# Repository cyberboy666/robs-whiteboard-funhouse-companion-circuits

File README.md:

View this project on [CADLAB.io](https://cadlab.io/project/23483). 

# robs-whiteboard-funhouse-companion-circuits

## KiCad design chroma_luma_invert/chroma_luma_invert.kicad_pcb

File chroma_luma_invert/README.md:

# v0.1 notes

Qty | Reference(s) | Value
--- | --- | ---
1 | C1 | 0.1u
2 | C2, C3 | 0.001u
1 | C4 | 0.001u
1 | C5 | 0.0001u
2 | C6, C7 | 0.01u
1 | D1 | 1n914
2 | J1, J2 | rca
1 | J3 | Barrel_Jack
1 | J4 | Conn_01x12
1 | R1 | 1.5k
2 | R2, R6 | 75
9 | R3, R4, R5, R9, R10, R12, R13, R17, R19 | 1k
1 | R7 | 1m
1 | R8 | 2.2
1 | R11 | 5.6k
2 | R14, R15 | 100
1 | R16 | 68k
5 | R18, R21, R23, R26, R27 | 10k
2 | R20, R25 | 15k
1 | R22 | 3.9k
1 | R24 | 39k
1 | RV1 | 10k_pot
1 | RV2 | 5k_pot
1 | RV3 | 100k_pot
1 | RV4 | 20k_pot
2 | SW1, SW2 | SW_SPST
1 | U1 | AD8044
1 | U3 | 4051
1 | U4 | LM317
2 | U5, U6 | LM311
3 | U7, U8, U10 | 74HC4538
1 | U9 | 4040

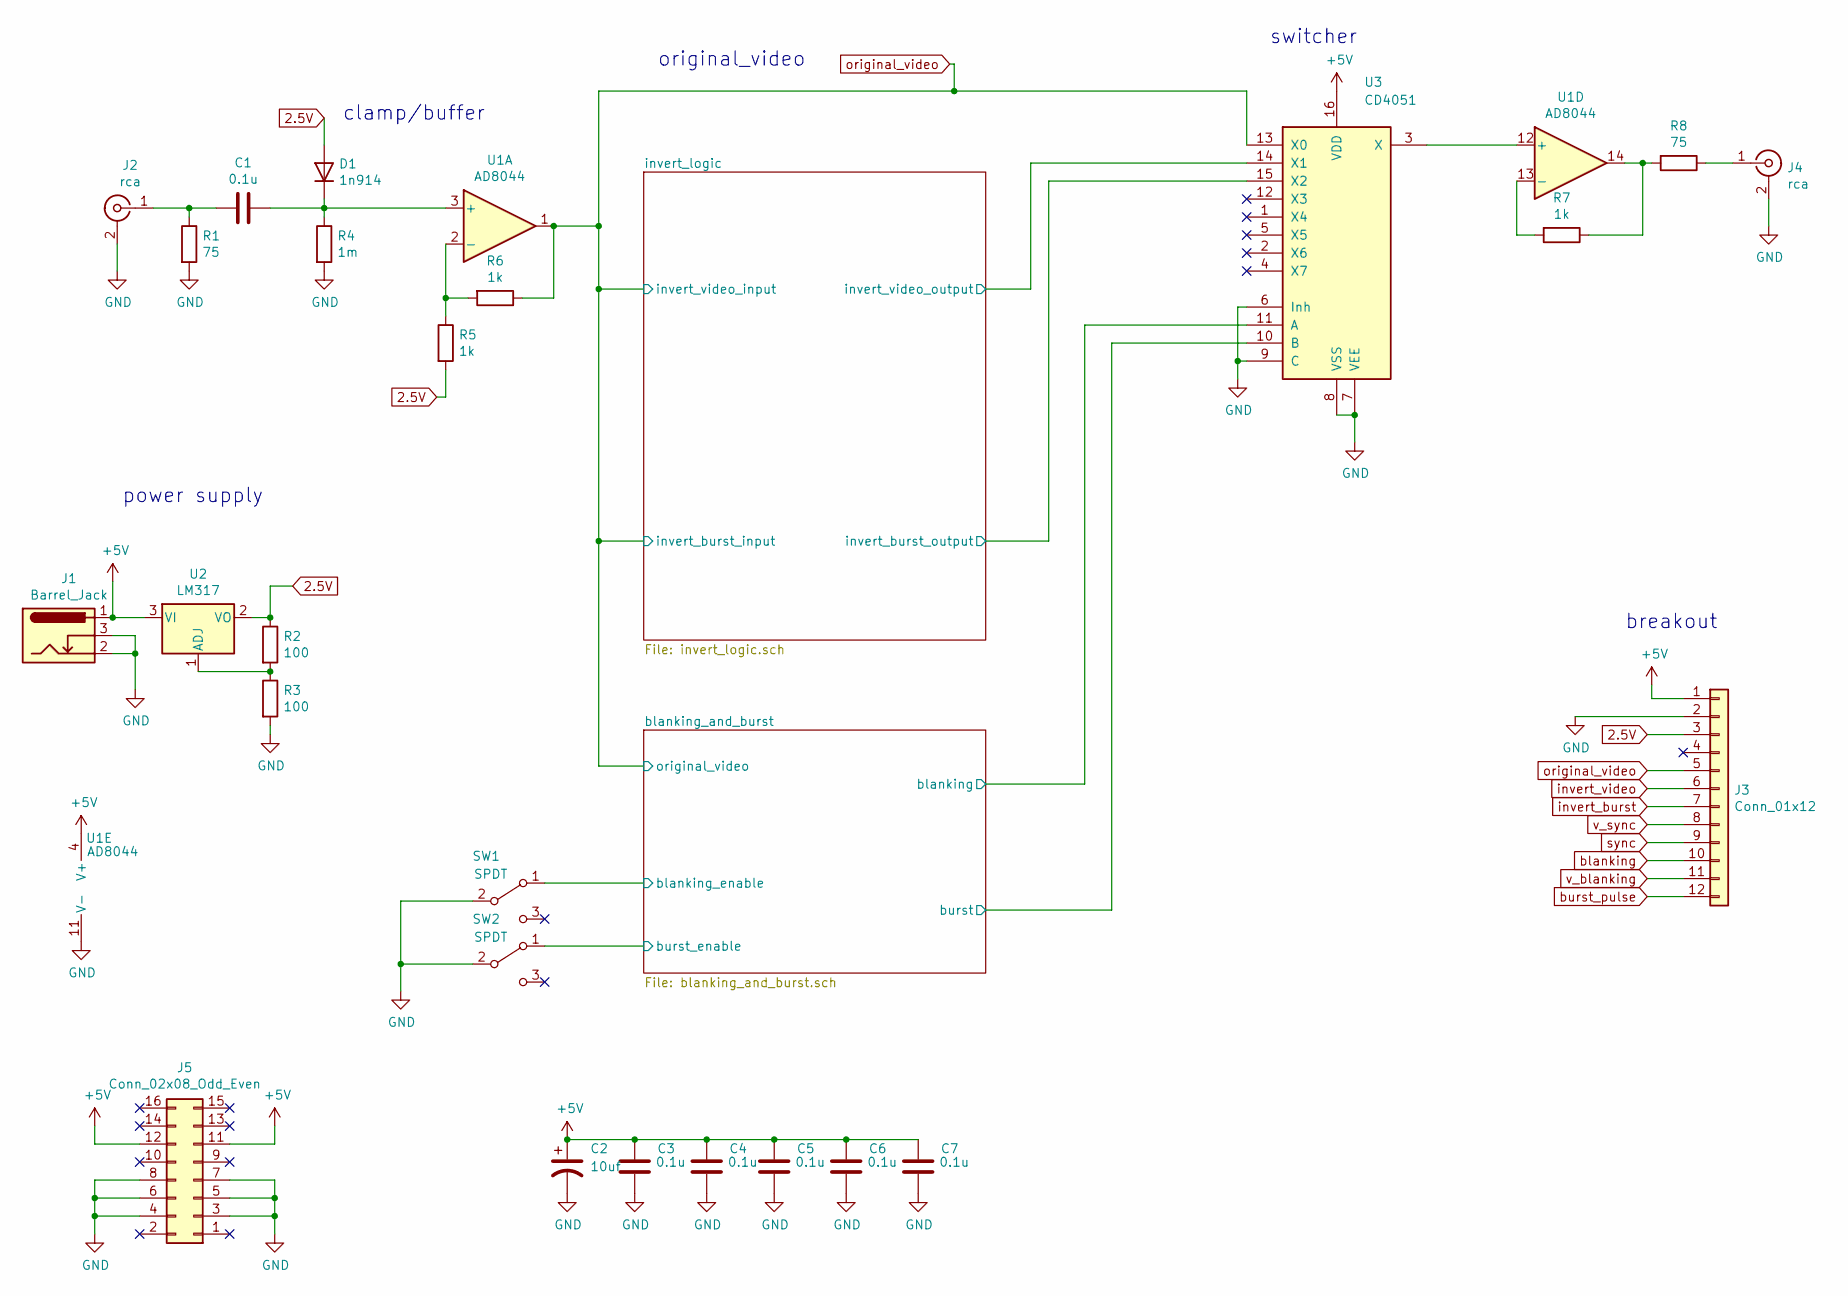
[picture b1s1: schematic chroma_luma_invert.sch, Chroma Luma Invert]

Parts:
C1, C3, C4, C5, C6, C7: 0.1u; C_Disc_D4.7mm_W2.5mm_P5.00mm
C2: 10uf; CP_Radial_D6.3mm_P2.50mm
D1: 1n914; D_DO-41_SOD81_P7.62mm_Horizontal
J1: Barrel_Jack; BarrelJack_Horizontal
J2, J4: rca; tht_vertical_rca
J3: Conn_01x12; PinHeader_1x12_P2.54mm_Vertical
J5: Conn_02x08_Odd_Even; PinHeader_2x08_P2.54mm_Vertical
R1, R8: 75; R_Axial_DIN0207_L6.3mm_D2.5mm_P7.62mm_Horizontal
R2, R3: 100; R_Axial_DIN0207_L6.3mm_D2.5mm_P7.62mm_Horizontal
R4: 1m; R_Axial_DIN0207_L6.3mm_D2.5mm_P7.62mm_Horizontal
R5, R6, R7: 1k; R_Axial_DIN0207_L6.3mm_D2.5mm_P7.62mm_Horizontal
SW1, SW2: SPDT; spdt_slide_switch_small_tayda
U1: AD8044; DIP+SOIC_14
U2: LM317; TO-220-3_Vertical
U3: CD4051; DIP-16_W7.62mm_LongPads

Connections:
2.5V: D1.2 (A), J3.3, R2.1, R5.2, U2.2 (VO); also elsewhere on the board
+5V: C2.1, C3.2, C4.2, C5.2, C6.2, C7.2, J1.1, J3.1, J5.11, J5.12, U1.4 (V+), U2.3 (VI), U3.16 (VDD); also elsewhere on the board
/blanking_and_burst/blanking_enable: SW1.1 (A); also elsewhere on the board
GND: C2.2, C3.1, C4.1, C5.1, C6.1, C7.1, J1.2, J1.3, J2.2 (Ext), J3.2, J4.2 (Ext), J5.3, J5.4, J5.5, J5.6, J5.7, J5.8, R1.2, R3.2, R4.2, SW1.2 (B), SW2.2 (B), U1.11 (V-), U3.6 (Inh), U3.7 (VEE), U3.8 (VSS), U3.9 (C); also elsewhere on the board
unnamed: C1.1, D1.1 (K), R4.1, U1.3 (+)
unnamed: C1.2, J2.1 (In), R1.1
unnamed: J4.1 (In), R8.1
unnamed: R2.2, R3.1, U2.1 (ADJ)
unnamed: R5.1, R6.2, U1.2 (-)
unnamed: R7.1, R8.2, U1.14
unnamed: R7.2, U1.13 (-)
unnamed: U1.12 (+), U3.3 (X)
blanking: J3.10, U3.11 (A); also elsewhere on the board
burst_pulse: J3.12, SW2.1 (A), U3.10 (B); also elsewhere on the board
invert_burst: J3.7, U3.15 (X2); also elsewhere on the board
invert_video: J3.6, U3.14 (X1); also elsewhere on the board
original_video: J3.5, R6.1, U1.1, U3.13 (X0); also elsewhere on the board
sync: J3.9; also elsewhere on the board
v_blanking: J3.11; also elsewhere on the board
v_sync: J3.8; also elsewhere on the board

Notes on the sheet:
clamp/buffer
original_video
switcher
power supply
breakout

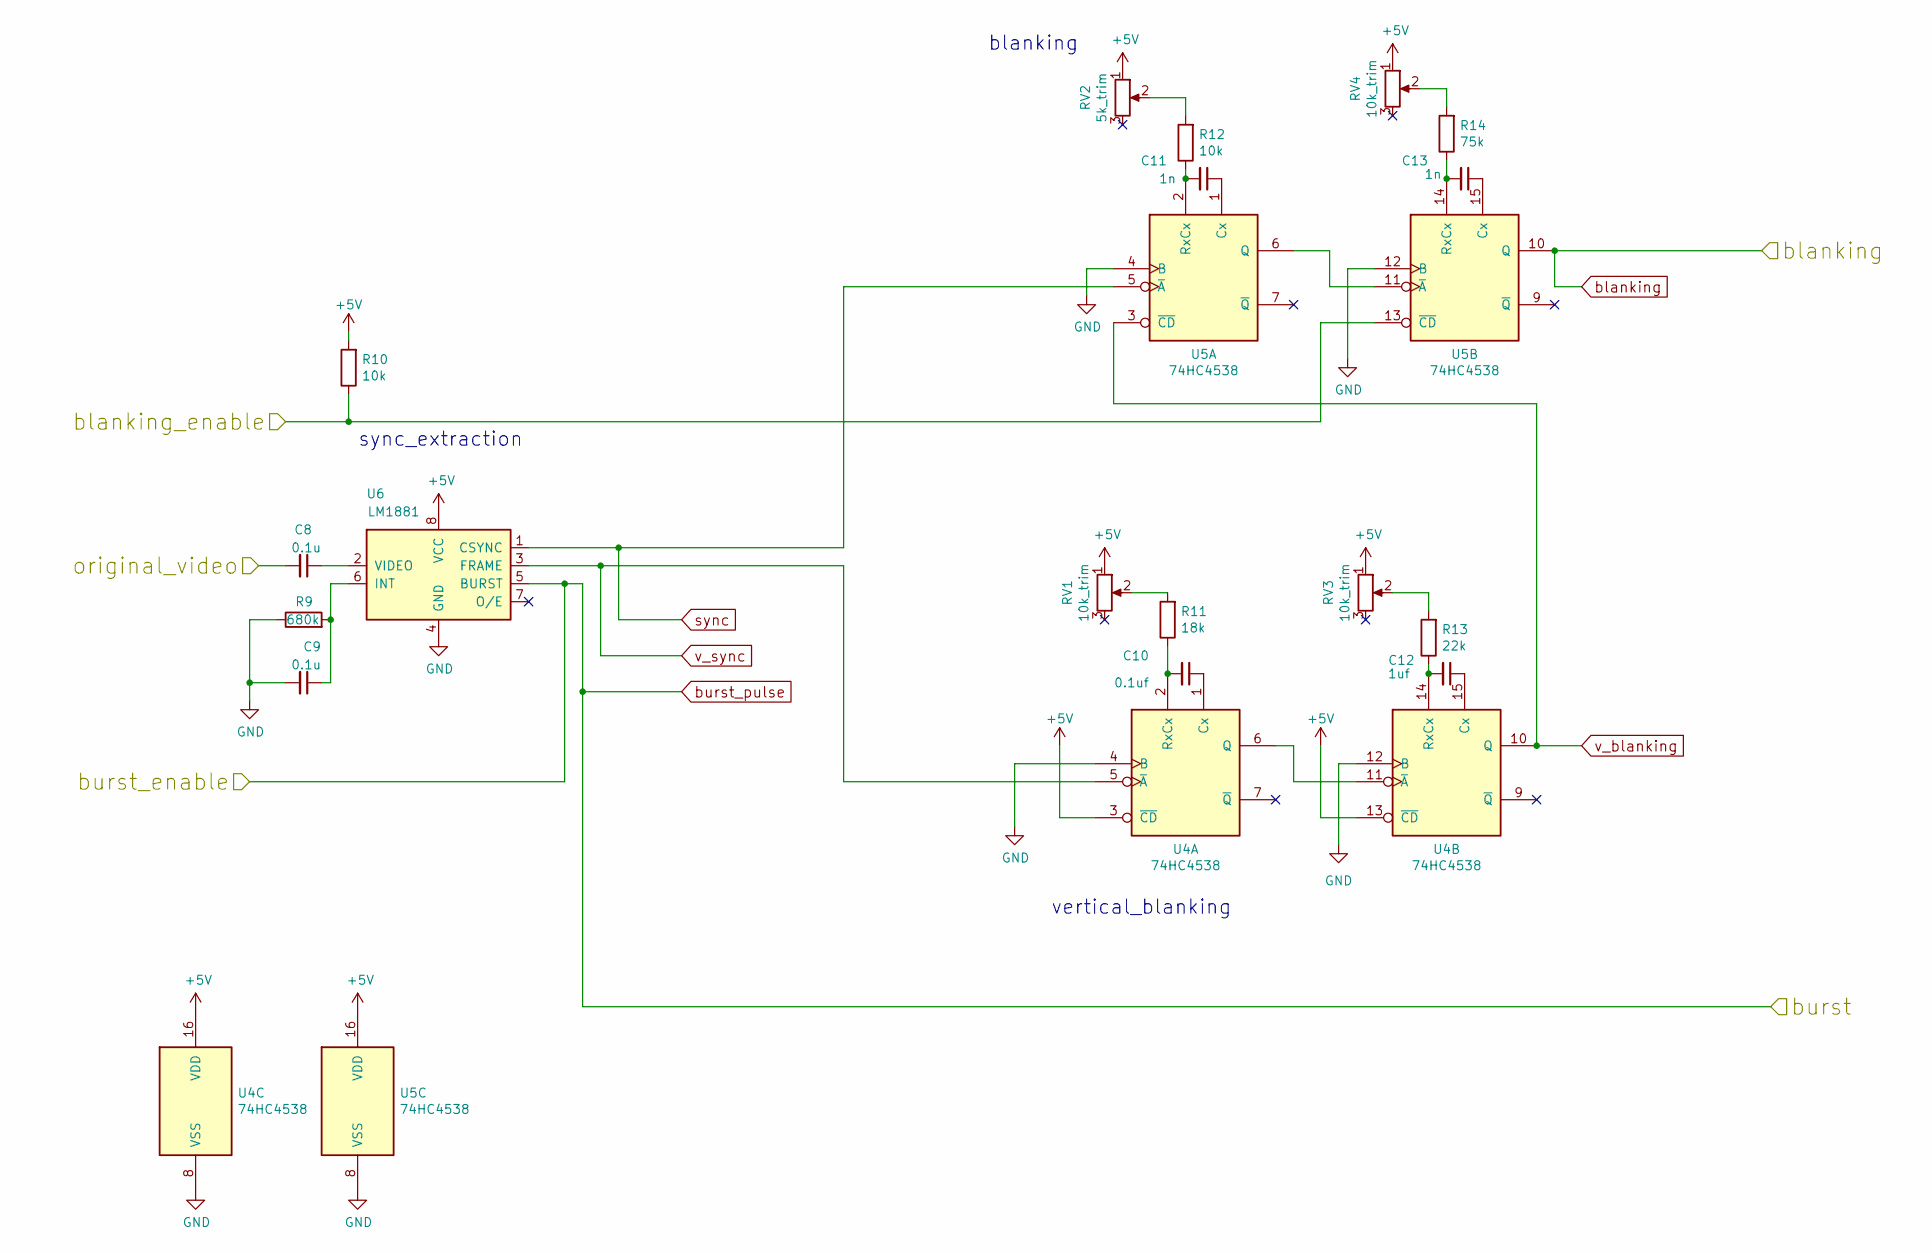
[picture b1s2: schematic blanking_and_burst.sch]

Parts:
C8, C9: 0.1u; C_Disc_D4.7mm_W2.5mm_P5.00mm
C10: 0.1uf; C_Disc_D4.7mm_W2.5mm_P5.00mm
C11, C13: 1n; C_Disc_D4.7mm_W2.5mm_P5.00mm
C12: 1uf; C_Disc_D4.7mm_W2.5mm_P5.00mm
R9: 680k; R_Axial_DIN0207_L6.3mm_D2.5mm_P7.62mm_Horizontal
R10, R12: 10k; R_Axial_DIN0207_L6.3mm_D2.5mm_P7.62mm_Horizontal
R11: 18k; R_Axial_DIN0207_L6.3mm_D2.5mm_P7.62mm_Horizontal
R13: 22k; R_Axial_DIN0207_L6.3mm_D2.5mm_P7.62mm_Horizontal
R14: 75k; R_Axial_DIN0207_L6.3mm_D2.5mm_P7.62mm_Horizontal
RV1, RV3, RV4: 10k_trim; tht_vertical_trimpot_3362
RV2: 5k_trim; tht_vertical_trimpot_3362
U4, U5: 74HC4538; DIP-16_W7.62mm_LongPads
U6: LM1881; DIP-SOIC-8

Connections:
+5V: R10.2, RV1.1, RV2.1, RV3.1, RV4.1, U4.3 (~CD), U4.13 (~CD), U4.16 (VDD), U5.16 (VDD), U6.8 (VCC); also elsewhere on the board
/blanking_and_burst/blanking_enable: R10.1, U5.13 (~CD); also elsewhere on the board
GND: C9.2, R9.1, U4.4 (B), U4.8 (VSS), U4.12 (B), U5.4 (B), U5.8 (VSS), U5.12 (B), U6.4 (GND); also elsewhere on the board
unnamed: C8.1, U6.2 (VIDEO)
unnamed: C9.1, R9.2, U6.6 (INT)
unnamed: C10.1, U4.1 (Cx)
unnamed: C10.2, R11.1, U4.2 (RxCx)
unnamed: C11.1, U5.1 (Cx)
unnamed: C11.2, R12.1, U5.2 (RxCx)
unnamed: C12.1, U4.15 (Cx)
unnamed: C12.2, R13.1, U4.14 (RxCx)
unnamed: C13.1, U5.15 (Cx)
unnamed: C13.2, R14.1, U5.14 (RxCx)
unnamed: R11.2, RV1.2
unnamed: R12.2, RV2.2
unnamed: R13.2, RV3.2
unnamed: R14.2, RV4.2
unnamed: U4.6 (Q), U4.11 (~A)
unnamed: U5.6 (Q), U5.11 (~A)
blanking: U5.10 (Q); also elsewhere on the board
burst_pulse: U6.5 (BURST); also elsewhere on the board
original_video: C8.2; also elsewhere on the board
sync: U5.5 (~A), U6.1 (CSYNC); also elsewhere on the board
v_blanking: U4.10 (Q), U5.3 (~CD); also elsewhere on the board
v_sync: U4.5 (~A), U6.3 (FRAME); also elsewhere on the board

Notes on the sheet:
sync_extraction
blanking
vertical_blanking

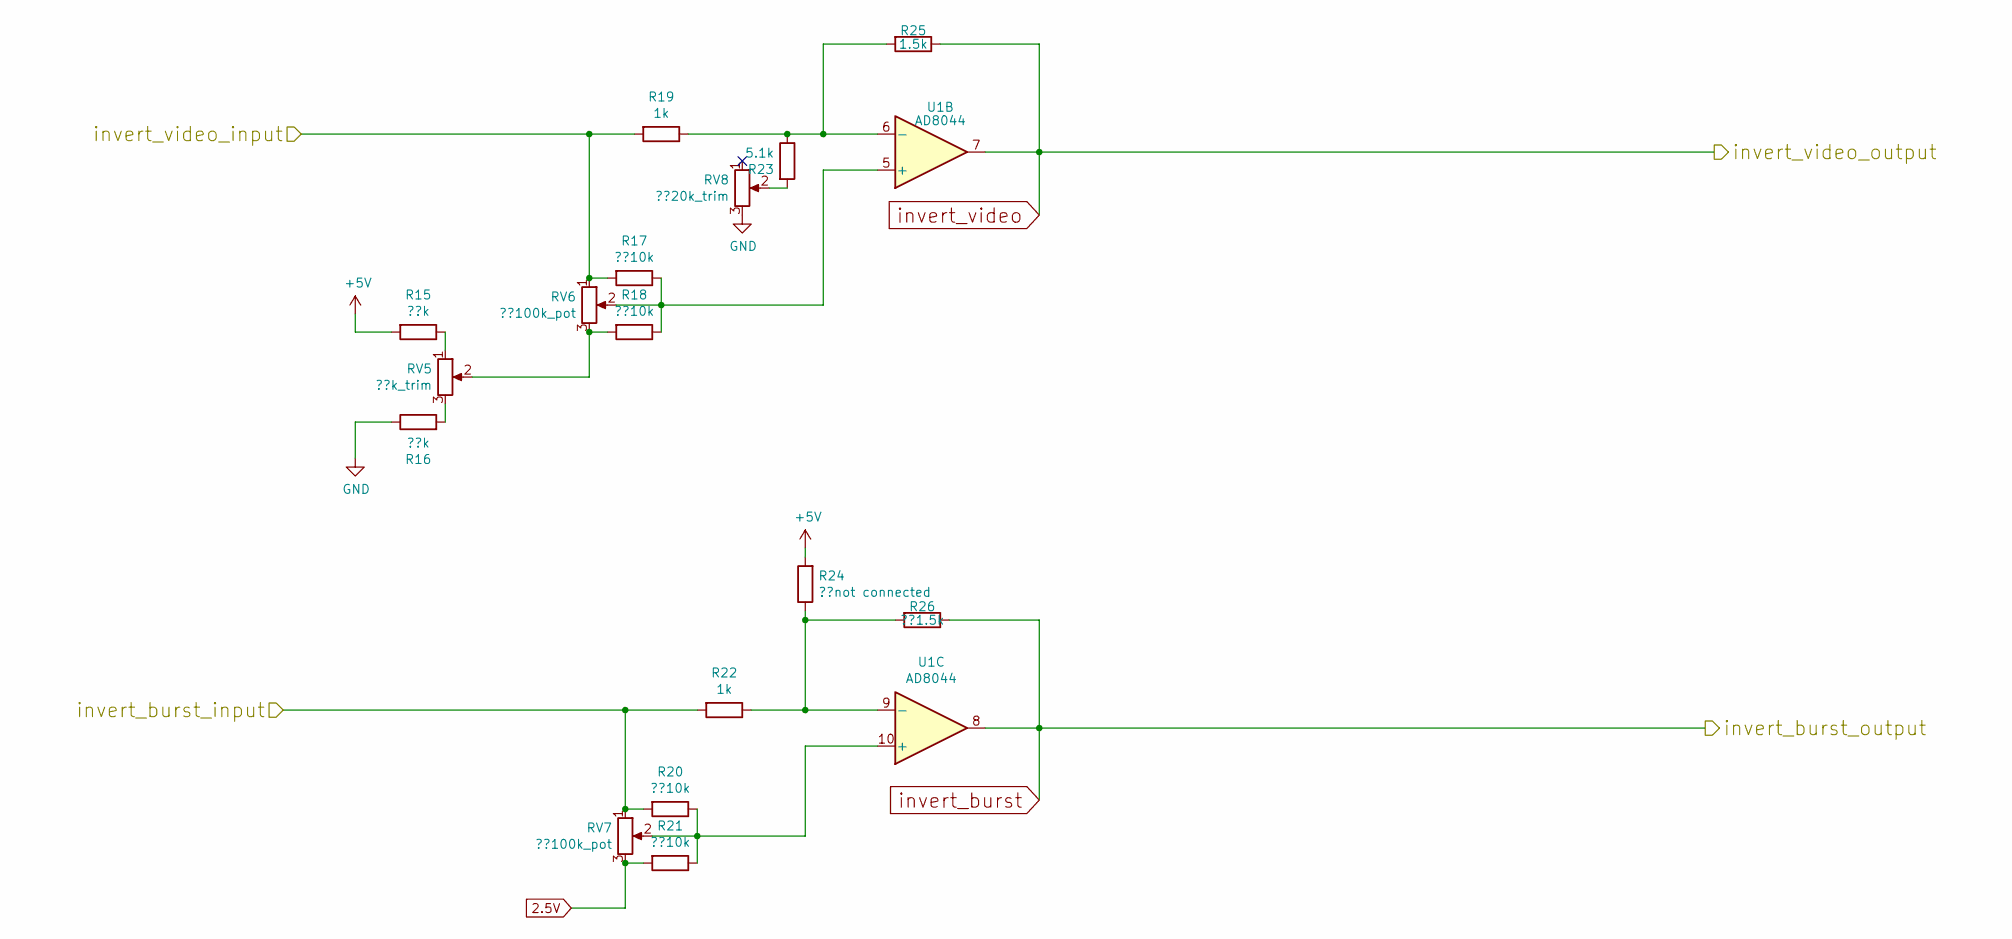
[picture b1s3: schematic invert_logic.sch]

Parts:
R15, R16: ??k; R_Axial_DIN0207_L6.3mm_D2.5mm_P7.62mm_Horizontal
R17, R18, R20, R21: ??10k; R_Axial_DIN0207_L6.3mm_D2.5mm_P7.62mm_Horizontal
R19, R22: 1k; R_Axial_DIN0207_L6.3mm_D2.5mm_P7.62mm_Horizontal
R23: 5.1k; R_Axial_DIN0207_L6.3mm_D2.5mm_P7.62mm_Horizontal
R24: ??not connected; R_Axial_DIN0207_L6.3mm_D2.5mm_P7.62mm_Horizontal
R25: 1.5k; R_Axial_DIN0207_L6.3mm_D2.5mm_P7.62mm_Horizontal
R26: ??1.5k; R_Axial_DIN0207_L6.3mm_D2.5mm_P7.62mm_Horizontal
RV5: ??k_trim; tht_vertical_trimpot_3362
RV6, RV7: ??100k_pot; Potentiometer_Vertical_Large
RV8: ??20k_trim; tht_vertical_trimpot_3362
U1: AD8044; DIP+SOIC_14

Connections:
2.5V: R21.2, RV7.3; also elsewhere on the board
+5V: R15.2, R24.2; also elsewhere on the board
GND: R16.1, RV8.3; also elsewhere on the board
unnamed: R15.1, RV5.1
unnamed: R16.2, RV5.3
unnamed: R17.1, R18.1, RV6.2, U1.5 (+)
unnamed: R18.2, RV5.2, RV6.3
unnamed: R19.1, R23.1, R25.2, U1.6 (-)
unnamed: R20.1, R21.1, RV7.2, U1.10 (+)
unnamed: R22.1, R24.1, R26.2, U1.9 (-)
unnamed: R23.2, RV8.2
invert_burst: R26.1, U1.8; also elsewhere on the board
invert_video: R25.1, U1.7; also elsewhere on the board
original_video: R17.2, R19.2, R20.2, R22.2, RV6.1, RV7.1; also elsewhere on the board

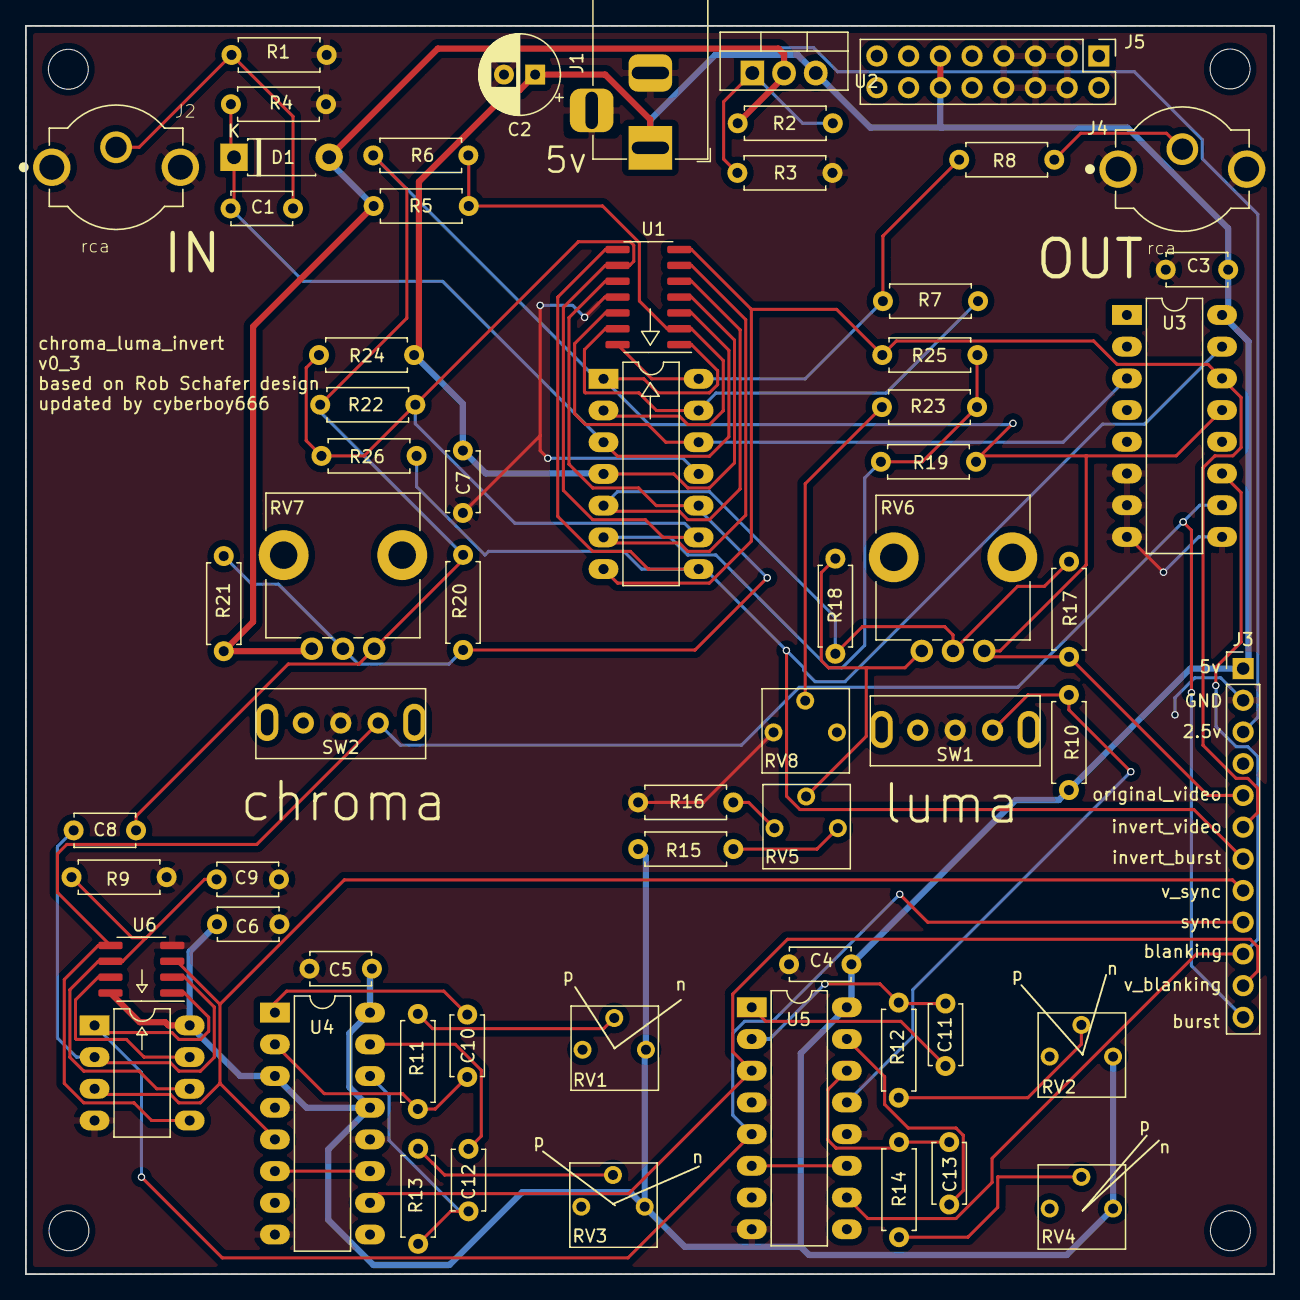
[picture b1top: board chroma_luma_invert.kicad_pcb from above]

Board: 2 copper layers, 100.0 x 100.0 mm, 61 parts (0 on the bottom side), 44 nets.

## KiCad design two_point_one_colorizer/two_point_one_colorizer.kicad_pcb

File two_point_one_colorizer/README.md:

# v_0_1 notes

Qty | Reference(s) | Value
--- | --- | ---
2 | C1, C2 | 33p
13 | C3, C5, C6, C7, C8, C9, C10, C11, C12, C13, C14, C15, C20 | 0.1u
1 | C4 | 10u
4 | C16, C17, C18, C19 | 10p
1 | D1 | 1n914
2 | J1, J2 | rca
1 | J3 | Mini-DIN-4
1 | J4 | Barrel_Jack
1 | J5 | Conn_01x03
1 | Q1 | 2N3904
1 | R1 | 1m
1 | R2 | 5k
1 | R3 | 100
3 | R4, R6, R8 | 75
4 | R5, R9, R27, R33 | 1k
1 | R7 | 1M
4 | R10, R13, R18, R22 | 10k
1 | R11 | 680k
2 | R12, R14 | 12k
4 | R15, R16, R19, R20 | 82k
2 | R17, R21 | 22k
2 | R23, R29 | R
4 | R24, R25, R30, R31 | 2.7k
2 | R26, R32 | 8.2k
2 | R28, R34 | 3.3k
6 | RV1, RV2, RV3, RV4, RV5, RV6 | 10k
2 | SW1, SW2 | SW_SPDT
1 | U1 | 74HC14
1 | U2 | 4053
1 | U3 | LM317
1 | U4 | LM1881
1 | U5 | 74HC86
1 | U6 | 4013
1 | U7 | LM393
2 | U8, U9 | 74LS221
1 | Y1 | Crystal

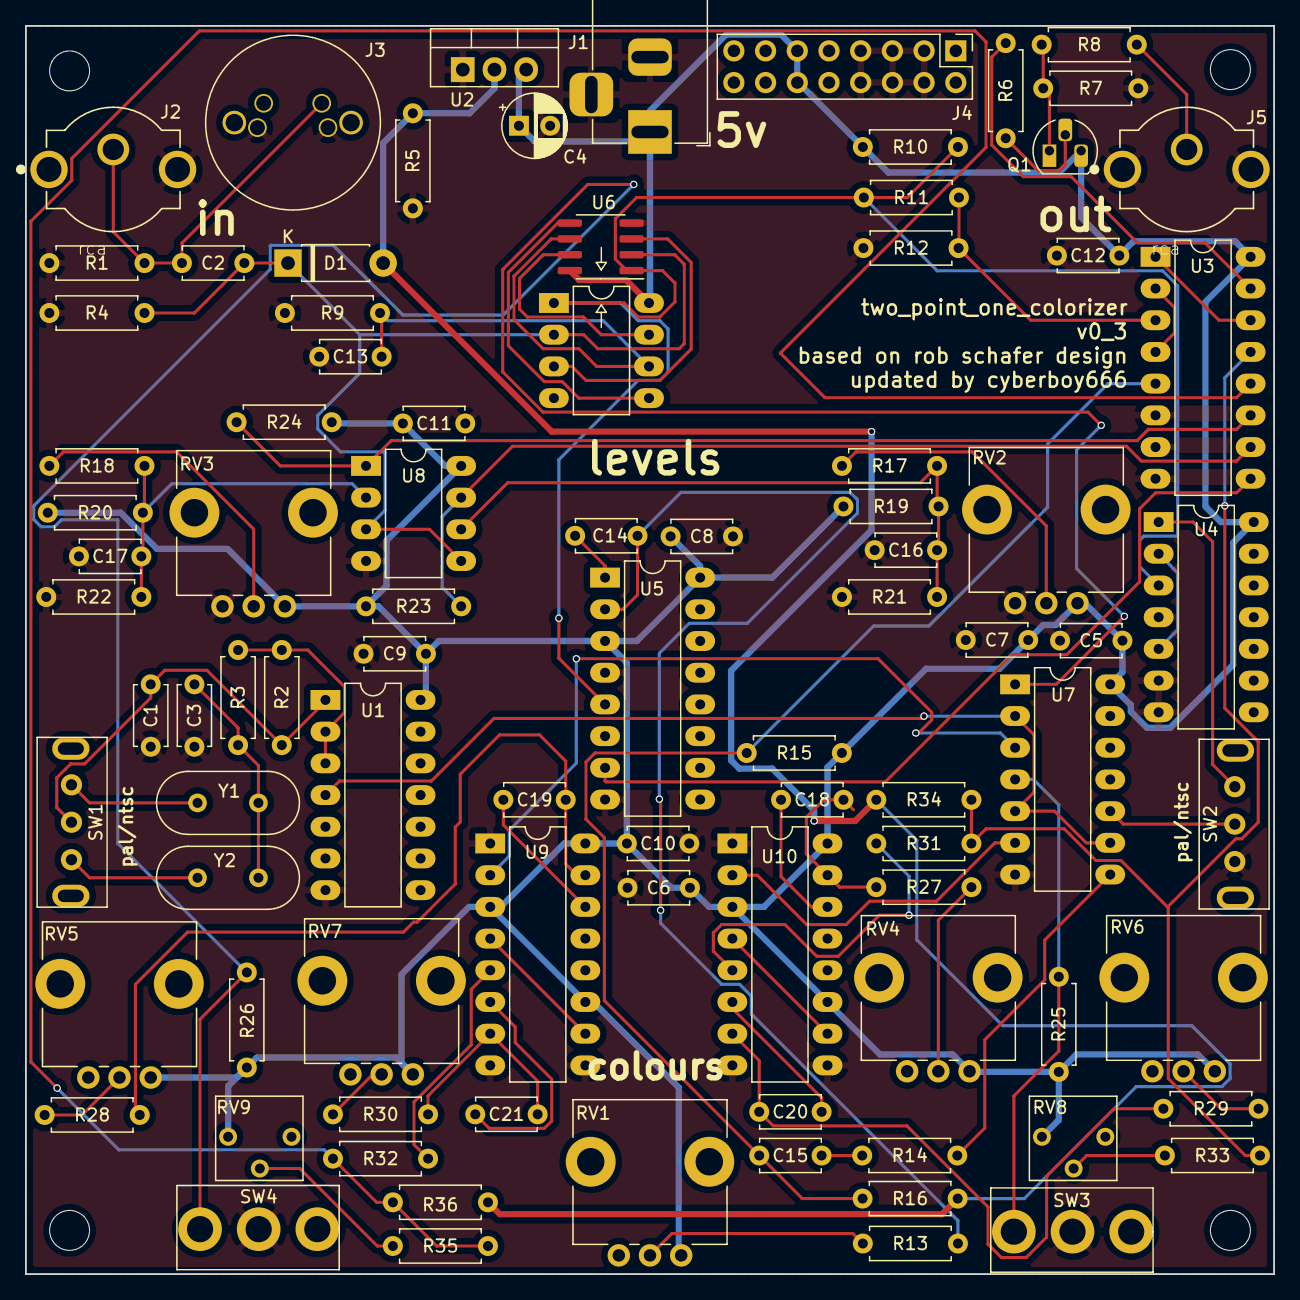
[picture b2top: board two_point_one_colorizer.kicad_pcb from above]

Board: 2 copper layers, 100.0 x 100.0 mm, 89 parts (0 on the bottom side), 60 nets.

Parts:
C1, C3: 33p; C_Disc_D4.7mm_W2.5mm_P5.00mm
C2, C5, C6, C7, C8, C9, C10, C11, C12, C13, C15, C16, C17: 0.1u; C_Disc_D4.7mm_W2.5mm_P5.00mm
C4: 10u; CP_Radial_D5.0mm_P2.50mm
C14: 0.1n; C_Disc_D4.7mm_W2.5mm_P5.00mm
C18, C19, C20, C21: 10p; C_Disc_D4.7mm_W2.5mm_P5.00mm
D1: 1n914; D_DO-41_SOD81_P7.62mm_Horizontal
J1: Barrel_Jack; BarrelJack_Horizontal
J2, J5: rca; tht_vertical_rca
J3: mini-din4; mini-din-4-vertical_KMDVLX-4S-N-1
J4: Conn_02x08_Odd_Even; PinHeader_2x08_P2.54mm_Vertical
Q1: 2N3904; TO-92L_HandSolder
R1, R5, R8: 75; R_Axial_DIN0207_L6.3mm_D2.5mm_P7.62mm_Horizontal
R2, R4: 1m; R_Axial_DIN0207_L6.3mm_D2.5mm_P7.62mm_Horizontal
R3: 5.1k; R_Axial_DIN0207_L6.3mm_D2.5mm_P7.62mm_Horizontal
R6: 100; R_Axial_DIN0207_L6.3mm_D2.5mm_P7.62mm_Horizontal
R7, R11, R31, R32: 1k; R_Axial_DIN0207_L6.3mm_D2.5mm_P7.62mm_Horizontal
R9: 680k; R_Axial_DIN0207_L6.3mm_D2.5mm_P7.62mm_Horizontal
R10, R13, R14, R21, R22, R25, R26: 10k; R_Axial_DIN0207_L6.3mm_D2.5mm_P7.62mm_Horizontal
R12: 1k (or 1.2k maybe); R_Axial_DIN0207_L6.3mm_D2.5mm_P7.62mm_Horizontal
R15: 12k; R_Axial_DIN0207_L6.3mm_D2.5mm_P7.62mm_Horizontal
R16, R33, R35: 1.5k; R_Axial_DIN0207_L6.3mm_D2.5mm_P7.62mm_Horizontal
R17, R18: 22k; R_Axial_DIN0207_L6.3mm_D2.5mm_P7.62mm_Horizontal
R19, R20, R23, R24: 82k; R_Axial_DIN0207_L6.3mm_D2.5mm_P7.62mm_Horizontal
R27, R28, R29, R30: 2.7k; R_Axial_DIN0207_L6.3mm_D2.5mm_P7.62mm_Horizontal
R34, R36: 3.3k; R_Axial_DIN0207_L6.3mm_D2.5mm_P7.62mm_Horizontal
RV1: 20k_pot; Potentiometer_Vertical_Large
RV2, RV3, RV4, RV5, RV6, RV7: 10k_pot; Potentiometer_Vertical_Large
RV8, RV9: 5k_trim; Pot_trim_3362_tayda
SW1, SW2: SPDT_slide; spdt_slide_switch_small_tayda
SW3, SW4: SPDT; mini_toggle_switch_tayda
U1: 4069; DIP-14_W7.62mm_LongPads
U2: LM317; TO-220-3_Vertical
U3: CD4053; DIP-16_W7.62mm_LongPads
U4: CD4013; DIP-14_W7.62mm_LongPads
U5: 74HC4538; DIP-16_W7.62mm_LongPads
U6: LM1881; DIP-SOIC-8
U7: 74HC86; DIP-14_W7.62mm_LongPads
U8: LM393; DIP-8_W7.62mm_LongPads
U9, U10: 74LS221; DIP-16_W7.62mm_LongPads
Y1, Y2: Crystal; Crystal_HC49-4H_Vertical

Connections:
1.25v: D1.2, R5.1, R16.1, R34.2, R36.2, U2.2
+5V: C4.1, C5.1, C6.1, C7.1, C8.1, C9.1, C10.1, C11.1, C12.1, J1.1, J4.11, J4.12, Q1.3, R10.1, R15.2, R19.1, R20.1, R23.1, R24.1, R25.1, R26.1, RV1.1, RV2.1, RV3.1, RV4.1, RV5.1, RV6.1, RV7.1, RV8.1, RV9.1, U1.14, U2.3, U3.16, U4.14, U5.3, U5.16, U6.8, U7.14, U8.8, U9.3, U9.11, U9.16, U10.3, U10.11, U10.16
/colours/colour1: R32.1, R35.2, R36.1, U3.12
/colours/colour2: R31.1, R33.2, R34.1, U3.13
/colours/crystal: U1.4, U7.2, U7.5, U7.9
/comparators/comparator1: R24.2, U3.11, U8.1
/comparators/comparator2: R23.2, U3.10, U8.7
/comparators/video: C2.1, D1.1, R4.1, U6.2, U8.3, U8.5
/sync_and_burst/black_and_sync: R11.1, R12.2, U3.3
/sync_and_burst/burst_pulse: U3.9, U5.7
/sync_and_burst/burst_signal: C15.1, R15.1, R16.2, U3.5
GND: C1.2, C3.2, C4.2, C5.2, C6.2, C7.2, C8.2, C9.2, C10.2, C11.2, C12.2, C13.1, C16.2, C17.2, J1.2, J1.3, J2.2, J3.1, J3.2, J4.3, J4.4, J4.5, J4.6, J4.7, J4.8, J5.2, R1.2, R4.2, R5.2, R7.2, R9.1, R12.1, R21.2, R22.2, RV2.3, RV3.3, SW2.1, SW3.2, SW4.2, U1.7, U2.1, U3.6, U3.7, U3.8, U4.4, U4.6, U4.7, U5.4, U5.8, U6.4, U7.7, U8.4, U9.1, U9.8, U9.9, U10.1, U10.8, U10.9
unnamed: C1.1, R2.2, SW1.2, U1.1
unnamed: C2.2, J2.1, J3.4, R1.1
unnamed: C3.1, R3.2, Y1.2, Y2.2
unnamed: C13.2, R9.2, U6.6
unnamed: C14.1, R13.2, U5.2
unnamed: C14.2, U5.1
unnamed: C15.2, R14.1
unnamed: C16.1, R17.1, R19.2, R21.1, U8.6
unnamed: C17.1, R18.1, R20.2, R22.1, U8.2
unnamed: C18.1, R27.2, U10.15
unnamed: C18.2, U10.14
unnamed: C19.1, R28.2, U9.15
unnamed: C19.2, U9.14
unnamed: C20.1, R29.2, U10.7
unnamed: C20.2, U10.6
unnamed: C21.1, R30.2, U9.7
unnamed: C21.2, U9.6
unnamed: J5.1, R8.1
unnamed: Q1.1, R7.1, R8.2
unnamed: Q1.2, R6.1
unnamed: R2.1, R3.1, U1.2, U1.3
unnamed: R6.2, U3.15
unnamed: R10.2, R11.2, U4.3, U5.5, U6.1
unnamed: R13.1, RV1.2
unnamed: R14.2, U7.8
unnamed: R17.2, RV2.2
unnamed: R18.2, RV3.2
unnamed: R25.2, SW3.1, U7.4
unnamed: R26.2, SW4.1, U7.1
unnamed: R27.1, RV4.2
unnamed: R28.1, RV5.2
unnamed: R29.1, RV6.2
unnamed: R30.1, RV7.2
unnamed: R31.2, U10.5
unnamed: R32.2, U9.5
unnamed: R33.1, RV8.2
unnamed: R35.1, RV9.2
unnamed: SW1.1, Y1.1
unnamed: SW1.3, Y2.1
unnamed: SW2.2, U7.10
unnamed: SW2.3, U4.1
unnamed: U4.2, U4.5
unnamed: U7.3, U9.2
unnamed: U9.4, U9.10
unnamed: U7.6, U10.2
unnamed: U10.4, U10.10
black_sync_and_burst: U3.2, U3.4
colours: U3.1, U3.14

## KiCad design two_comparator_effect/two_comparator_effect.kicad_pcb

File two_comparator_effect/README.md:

# two_comparator_effect

## lessons

this circuit is based on one described by Rob Schafer in:

- [Lesson 1 - Comparators](https://www.youtube.com/watch?v=ml8xnRFdcHY)
- [Lesson 2 - Clamping](https://www.youtube.com/watch?v=FymrxKLHy6c)

also see: [original schematic](https://www.youtube.com/watch?v=MSNrXUDO9DE) and [clamping scope example](https://www.youtube.com/watch?v=vQ15EZKisZ8)

## adaption

see this [scanlines thread](https://scanlines.xyz/t/whiteboard-schoolhouse-companion-circuits/127) for discussion on this project

video demos from this adaption:

- [2comparatorFx+recurboy](https://videos.scanlines.xyz/videos/watch/49ce42f5-12a4-4f6e-85ff-bbef453d9e1e)
- [2comparatorFx+recurboy_p2](https://videos.scanlines.xyz/videos/watch/e029e6a6-3494-4a65-8555-49e3c94d06a6)

# v0.2 bom:

## [interactive bom](https://htmlpreview.github.io/?https://github.com/langolierz/robs-whiteboard-funhouse-companion-circuits/blob/master/two_comparator_effect/bom/ibom.html)

Qty | Reference(s) | Value
--- | --- | ---
3 | C1, C2, C3 | 1u
1 | C4 | 0.1u
1 | D1 | 1n914
2 | J1, J2 | RCA
1 | J3 | Barrel_Jack
1 | Q1 | 2N3904
2 | R1, R5 | 4.7k
2 | R2, R15 | 1k
3 | R3, R4, R7 | 1.2k
1 | R6 | 680
2 | R8, R10 | 75
1 | R9 | 150k
1 | R11 | 47
1 | R12 | 470
1 | R13 | 180
1 | R14 | 1.5k
1 | R16 | 100
2 | RV1, RV2 | 1k
1 | U1 | LM339
1 | U2 | LM317

# build instructions:

what you need:

- soldering iron
- solder
- tin/sponge
- wire clippers
- cvbs video source
- cvbs video display
- 5v barrel plug powersupply (either to wall or to usb)

maybe useful: 

- solder braid/pump
- multi meter

## building

- note on soldering: try to remember to heat pad first (2-3seconds), then add solder, then continue to heat (1-2seconds)

- start with the resistors, taking care place the correct value resisitor in the correct footprint (if you are unsure of the value can use [this](http://resistor.cherryjourney.pt/) calculator ) , direction does not matter. lets try placing half the resistors first (up to r6) then soldering and trimming , then placing the second half

- next lets do capicitors: will need to idenitfy which is 0.1u (will say 104, while the others say 105 on it), then place them all and solder and trim.

- now lets place diodes and transistors. _take note of the direction on the diode_ - black bar on component matching black bar on footprint. also you need to read the transistors to tell which is which - they are not the same ! be careful when soldering the to92 parts the pads are very close - this is the hardest part ! (i soldered the outer legs first, trimmed these and then soldered inner)

- now lets do the ic socket -> _make sure the direction is correct!_ place in and fold two corner legs to hold in place, then solder all legs. you can place the ic in now too

- finally lets place the control parts, starting with the power jack (can use something under teh board to balance it while you solder), next place the rca jacks and pots. be generous with the solder here -> this is to strengthen the mechanical connections aswell as making electrical ones

## testing

and the circuit is done ! check for any solder bridges or unsoldered joins - use a multimeter to be sure if you have one. time to test. best to start by setting up your cvbs video source and plugging directly into the cvbs video display -> is this giving the expected image ?

next power the device (no funny smells?) , and try patching the cvbs source through the two_comparator_effect -> anything on the screen ? try adjusting the knobs - at the lower end might drop out..

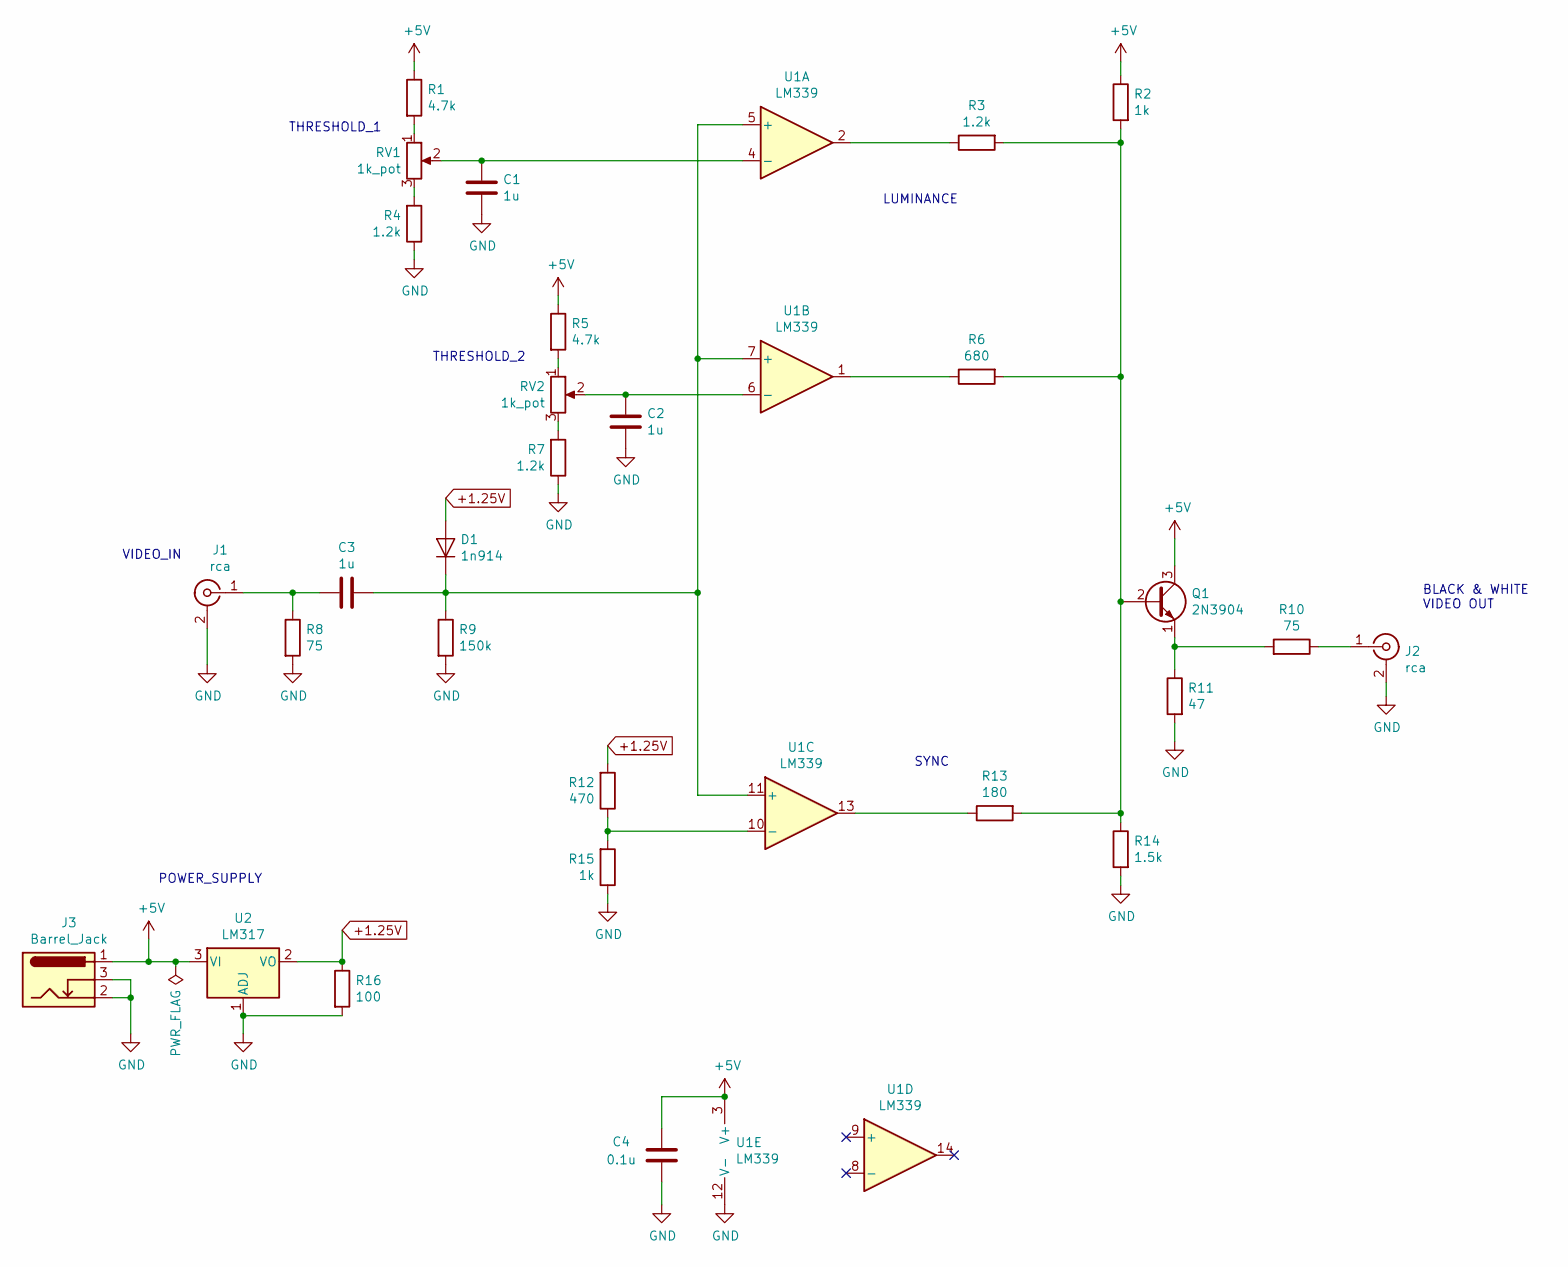
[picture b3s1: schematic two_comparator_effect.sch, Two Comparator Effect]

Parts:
C1, C2, C3: 1u; C_Disc_D4.7mm_W2.5mm_P5.00mm
C4: 0.1u; C_Disc_D4.7mm_W2.5mm_P5.00mm
D1: 1n914; D_A-405_P7.62mm_Horizontal
J1, J2: rca; tht_rca_vertical
J3: Barrel_Jack; BarrelJack_Horizontal
Q1: 2N3904; TO-92_HandSolder
R1, R5: 4.7k; R_Axial_DIN0207_L6.3mm_D2.5mm_P7.62mm_Horizontal
R2, R15: 1k; R_Axial_DIN0207_L6.3mm_D2.5mm_P7.62mm_Horizontal
R3, R4, R7: 1.2k; R_Axial_DIN0207_L6.3mm_D2.5mm_P7.62mm_Horizontal
R6: 680; R_Axial_DIN0207_L6.3mm_D2.5mm_P7.62mm_Horizontal
R8, R10: 75; R_Axial_DIN0207_L6.3mm_D2.5mm_P7.62mm_Horizontal
R9: 150k; R_Axial_DIN0207_L6.3mm_D2.5mm_P7.62mm_Horizontal
R11: 47; R_Axial_DIN0207_L6.3mm_D2.5mm_P7.62mm_Horizontal
R12: 470; R_Axial_DIN0207_L6.3mm_D2.5mm_P7.62mm_Horizontal
R13: 180; R_Axial_DIN0207_L6.3mm_D2.5mm_P7.62mm_Horizontal
R14: 1.5k; R_Axial_DIN0207_L6.3mm_D2.5mm_P7.62mm_Horizontal
R16: 100; R_Axial_DIN0207_L6.3mm_D2.5mm_P7.62mm_Horizontal
RV1, RV2: 1k_pot; Potentiometer_Vertical_Large
U1: LM339; DIP-14_W7.62mm_LongPads
U2: LM317; TO-92_HandSolder

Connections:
+1.25V: D1.2 (A), R12.2, R16.1, U2.2 (VO)
+5V: C4.1, J3.1, Q1.3 (C), R1.1, R2.1, R5.1, U1.3 (V+), U2.3 (VI)
GND: C1.1, C2.1, C4.2, J1.2 (Ext), J2.2 (Ext), J3.2, J3.3, R4.1, R7.1, R8.2, R9.2, R11.2, R14.2, R15.1, R16.2, U1.12 (V-), U2.1 (ADJ)
unnamed: C1.2, RV1.2, U1.4 (-)
unnamed: C2.2, RV2.2, U1.6 (-)
unnamed: C3.1, D1.1 (K), R9.1, U1.5 (+), U1.7 (+), U1.11 (+)
unnamed: C3.2, J1.1 (In), R8.1
unnamed: J2.1 (In), R10.1
unnamed: Q1.1 (E), R10.2, R11.1
unnamed: Q1.2 (B), R2.2, R3.2, R6.2, R13.2, R14.1
unnamed: R1.2, RV1.1
unnamed: R3.1, U1.2
unnamed: R4.2, RV1.3
unnamed: R5.2, RV2.1
unnamed: R6.1, U1.1
unnamed: R7.2, RV2.3
unnamed: R12.1, R15.2, U1.10 (-)
unnamed: R13.1, U1.13

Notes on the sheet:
SYNC
VIDEO_IN
BLACK & WHITE VIDEO OUT
THRESHOLD_2
LUMINANCE
THRESHOLD_1
POWER_SUPPLY

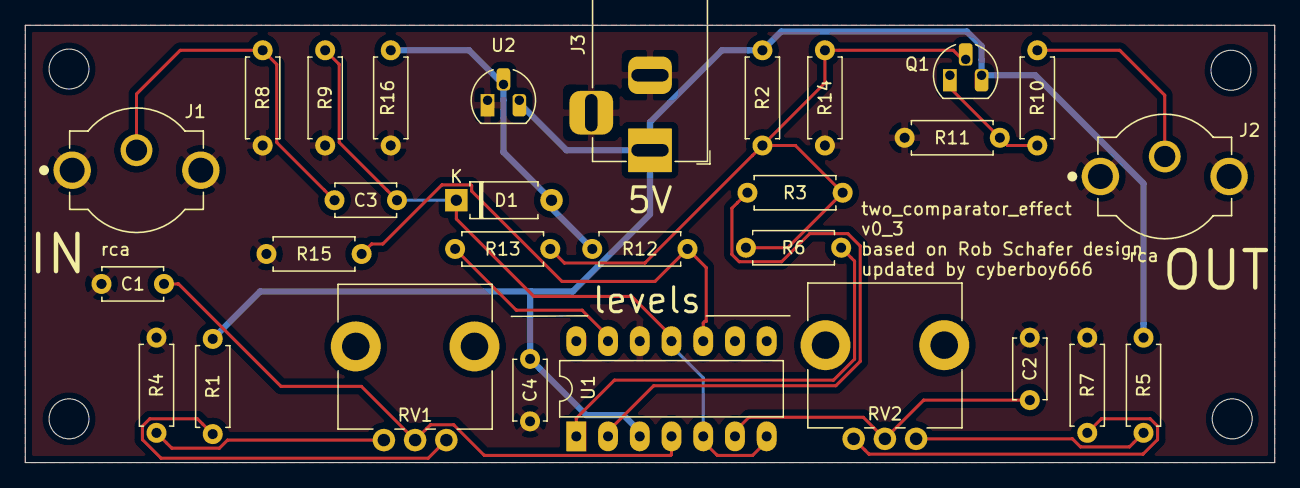
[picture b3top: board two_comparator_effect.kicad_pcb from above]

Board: 2 copper layers, 100.0 x 35.0 mm, 29 parts (0 on the bottom side), 18 nets.

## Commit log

2020-06-12 schematics
2020-06-13 routing boards
2020-06-13 updates to circuit
2020-06-14 updated opamp
2020-08-28 updated two_comparator and added two_point_one
2020-11-02 update circuits
2020-11-02 Backlink to CADLAB.io has been added.
2020-11-02 add svg schematic
2020-11-02 example change to svg
2020-12-17 small changes
2021-07-14 revised all boards
2021-09-27 update for new chroma_luma circuit
2021-10-11 working on nexr version for colorizer and inverter
2021-10-11 lay out colorizer
2021-12-10 newest circuit revisions
2022-01-10 migrate away from this repo
